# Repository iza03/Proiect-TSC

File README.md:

# DeskAssistant v1.5 – README

## Diagrama bloc

---

## Bill of Materials (BoM)

# Bill of Materials

| Componenta | Link |
|------------|------|
| SAMACSYS_PARTS_USB4110-GF-A | [https://componentsearchengine.com/part-view/USB4110-GF-A/GCT%20(GLOBAL%20CONNECTOR%20TECHNOLOGY)](https://componentsearchengine.com/part-view/USB4110-GF-A/GCT%20(GLOBAL%20CONNECTOR%20TECHNOLOGY)) |
| SI1308EDL-T1-GE3 | [https://componentsearchengine.com/part-view/SI1308EDL-T1-GE3/Vishay](https://componentsearchengine.com/part-view/SI1308EDL-T1-GE3/Vishay) |
| SJ | [https://grabcad.com/library/solder-jumpers-1](https://grabcad.com/library/solder-jumpers-1) |
| USBLC6-2SC6Y | [https://www.snapeda.com/parts/USBLC6-2SC6Y/STMicroelectronics/view-part/?ref=eda](https://www.snapeda.com/parts/USBLC6-2SC6Y/STMicroelectronics/view-part/?ref=eda) |
| W25Q512JVEIQ | [https://www.snapeda.com/parts/W25Q512JVEIQ/Winbond+Electronics/view-part/?ref=eda](https://www.snapeda.com/parts/W25Q512JVEIQ/Winbond+Electronics/view-part/?ref=eda) |
| ESP32_WROVER_EAGLE-LTSPICE_RR0402 | [https://www.snapeda.com/parts/RC0402FR-07226RL/Yageo/view-part/](https://www.snapeda.com/parts/RC0402FR-07226RL/Yageo/view-part/) |
| ESP32C6_VARISTORCN1812 | [https://www.mouser.co.uk/ProductDetail/EPCOS-TDK/B72520T0350K062?qs=dEfas%2FXlABIszF52uu7vrg%3D%3D](https://www.mouser.co.uk/ProductDetail/EPCOS-TDK/B72520T0350K062?qs=dEfas%2FXlABIszF52uu7vrg%3D%3D) |
| FH34SRJ-24S-0.5SH_99_ | [https://componentsearchengine.com/part-view/XC6220A331MR-G/Torex](https://componentsearchengine.com/part-view/XC6220A331MR-G/Torex) |
| MAX17048G+T10 | [https://www.snapeda.com/parts/MAX17048G+T10/Analog+Devices/view-part/?ref=eda](https://www.snapeda.com/parts/MAX17048G+T10/Analog+Devices/view-part/?ref=eda) |
| MBR0530 | [https://ro.mouser.com/ProductDetail/KYOCERA-AVX/SD0805S020S1R0?qs=jCA%252BPfw4LHbpkAoSnwrdjw%3D%3D](https://ro.mouser.com/ProductDetail/KYOCERA-AVX/SD0805S020S1R0?qs=jCA%252BPfw4LHbpkAoSnwrdjw%3D%3D) |
| PGB1010603MR | [https://www.snapeda.com/parts/PGB1010603MR/Littelfuse/view-part/?ref=eda](https://www.snapeda.com/parts/PGB1010603MR/Littelfuse/view-part/?ref=eda) |
| RCL_CPOL-EUCT3528 | [https://ro.mouser.com/ProductDetail/Vishay-Sprague/TR3B106K025C1300?qs=jCGqFXxTmLdffnuDkXzk1g%3D%3D](https://ro.mouser.com/ProductDetail/Vishay-Sprague/TR3B106K025C1300?qs=jCGqFXxTmLdffnuDkXzk1g%3D%3D) |
| 112A-TAAR-R03_ATTEND | [https://store.comet.bg/en/Catalogue/Product/43497/](https://store.comet.bg/en/Catalogue/Product/43497/) |
| 744043680IND_4828-WE-TPC_WRE | [https://www.digikey.sg/en/models/1638515](https://www.digikey.sg/en/models/1638515) |
| BD5229G-TR | [https://componentsearchengine.com/part-view/BD5229G-TR/ROHM%20Semiconductor](https://componentsearchengine.com/part-view/BD5229G-TR/ROHM%20Semiconductor) |
| DS3231SN | [https://www.snapeda.com/parts/DS3231SN%23/Analog+Devices/view-part/?ref=eda](https://www.snapeda.com/parts/DS3231SN%23/Analog+Devices/view-part/?ref=eda) |
| ESP32-C6-WROOM-1-N8 | [https://www.snapeda.com/parts/ESP32-C6-WROOM-1-N8/Espressif+Systems/view-part/?ref=eda](https://www.snapeda.com/parts/ESP32-C6-WROOM-1-N8/Espressif+Systems/view-part/?ref=eda) |
| MCP73831 | [https://www.digikey.com/en/models/1874108](https://www.digikey.com/en/models/1874108) |
| XC6220A331MR-G | [https://componentsearchengine.com/part-view/XC6220A331MR-G/Torex](https://componentsearchengine.com/part-view/XC6220A331MR-G/Torex) |
| QWIIC_CONNECTORJS-1MM | [https://www.snapeda.com/parts/PRT-14417/SparkFun/view-part/](https://www.snapeda.com/parts/PRT-14417/SparkFun/view-part/) |
| BUTTON_CUSYOMV1 | [https://industry.panasonic.com/global/en/downloads?tab=cad&small_g_cd=203&part_no=EVQPUJ02K&q=RVZRUFVKMDJLJTdDMTMlN0MyMDMlN0MzNDU5JTdDMSU3QyU3QyU3Q2ZhbHNl](https://industry.panasonic.com/global/en/downloads?tab=cad&small_g_cd=203&part_no=EVQPUJ02K&q=RVZRUFVKMDJLJTdDMTMlN0MyMDMlN0MzNDU5JTdDMSU3QyU3QyU3Q2ZhbHNl) |
| ESP32_WROVER_EAGLE-LTSPICE_CC0402 | [https://componentsearchengine.com/part-view/CC0402MRX5R5BB106/YAGEO](https://componentsearchengine.com/part-view/CC0402MRX5R5BB106/YAGEO) |
| CPH3225A | [https://www.snapeda.com/parts/CPH3225A/Seiko+Instruments/view-part/?ref=eda](https://www.snapeda.com/parts/CPH3225A/Seiko+Instruments/view-part/?ref=eda) |
| ADAFRUIT_LEDCHIP-LED0603 | [https://www.snapeda.com/parts/KP-1608SURCK/Kingbright/view-part/?ref=search&t=LED%200603](https://www.snapeda.com/parts/KP-1608SURCK/Kingbright/view-part/?ref=search&t=LED%200603) |
| ESP32_WROVER_BME680_BME680 | [https://www.snapeda.com/parts/BME680/Bosch/view-part/?welcome=home](https://www.snapeda.com/parts/BME680/Bosch/view-part/?welcome=home) |
| ESP32_WROVER_SPARKFUN-DISCRETESEMI_MOSFET_PCH-DMG2305UX-7 | [https://componentsearchengine.com/part-view/DMG2305UX-7/Diodes%20Incorporated](https://componentsearchengine.com/part-view/DMG2305UX-7/Diodes%20Incorporated) |

---

## Funcționalități hardware

### 1. Microcontroller – ESP32-C6-WROOM-1-N8
- **Wireless:** WiFi 6, BLE 5.0, Zigbee, Thread
- **Interfețe:** UART, I²C, SPI, USB, ADC, PWM
- **Rol:** Unitate centrală de control, achiziție date, comunicare cu periferice și backend.

### 2. Senzori
- **BME688**: măsoară temperatură, umiditate, presiune și compuși organici volatili (VOC)
  - **Interfață**: I²C
- **DS3231SN**: RTC (Real Time Clock)
  - **Interfață**: I²C
- **MAX17048**: fuel gauge pentru baterie
  - **Interfață**: I²C

### 3. Memorie externă
- **W25Q512JVEIQ**
  - **Tip**: NOR Flash, 512Mbit
  - **Interfață**: SPI

### 4. Managementul energiei
- **MCP73831**: încărcător Li-Ion
- **MAX17048**: monitorizare baterie
- **BD5229G-TR**: LDO pentru 2.9V stabil
- **Diodă Schottky, MOSFET, varistor**: protecție la supratensiuni și polarizare inversă

### 5. Conectivitate și I/O
- **USB4110-GF-A**: conector USB-C pentru alimentare/comunicare
- **QWIIC connector**: I²C modular pentru senzori plug-and-play
- **LED status** și **buton fizic** (boot/reset sau input utilizator)

---

## Conexiuni GPIO la ESP32-C6

| Componentă | Interfață | GPIO ESP32-C6 | Funcție |
|------------|-----------|----------------|---------|
| BME688 / DS3231 / MAX17048 | I²C | GPIO8 (SDA), GPIO9 (SCL) | Magistrală partajată |
| W25Q512JVEIQ | SPI | GPIO4 (MOSI), GPIO5 (MISO), GPIO6 (CLK), GPIO7 (CS) | Comunicare cu flash extern |
| LED status | GPIO | GPIO3 | Indicator status / PWM |
| Buton | GPIO + Pull-up | GPIO0 | Reset / boot / input utilizator |
| MCP73831 – STAT | GPIO | GPIO10 | Monitorizare stare încărcare |
| MAX17048 – ALERT | GPIO (Interrupt) | GPIO1 | Notificare SoC critic |
| USB-C – D+ / D- | USB | GPIO18 (D+), GPIO19 (D-) | Comunicare USB nativă |

---

## Estimare consum energetic

| Componentă | Consum tipic |
|------------|--------------|
| ESP32-C6 | ~130 mA (activ) |
| BME688 | ~3.1 µA |
| DS3231 | ~200 nA |
| MAX17048 | ~23 µA |
| MCP73831 | până la 500 mA (în încărcare) |
| LED-uri | 2–10 mA |

**Consum total în mod activ:** aprox. **150–180 mA**

### Randări PCB și design fizic

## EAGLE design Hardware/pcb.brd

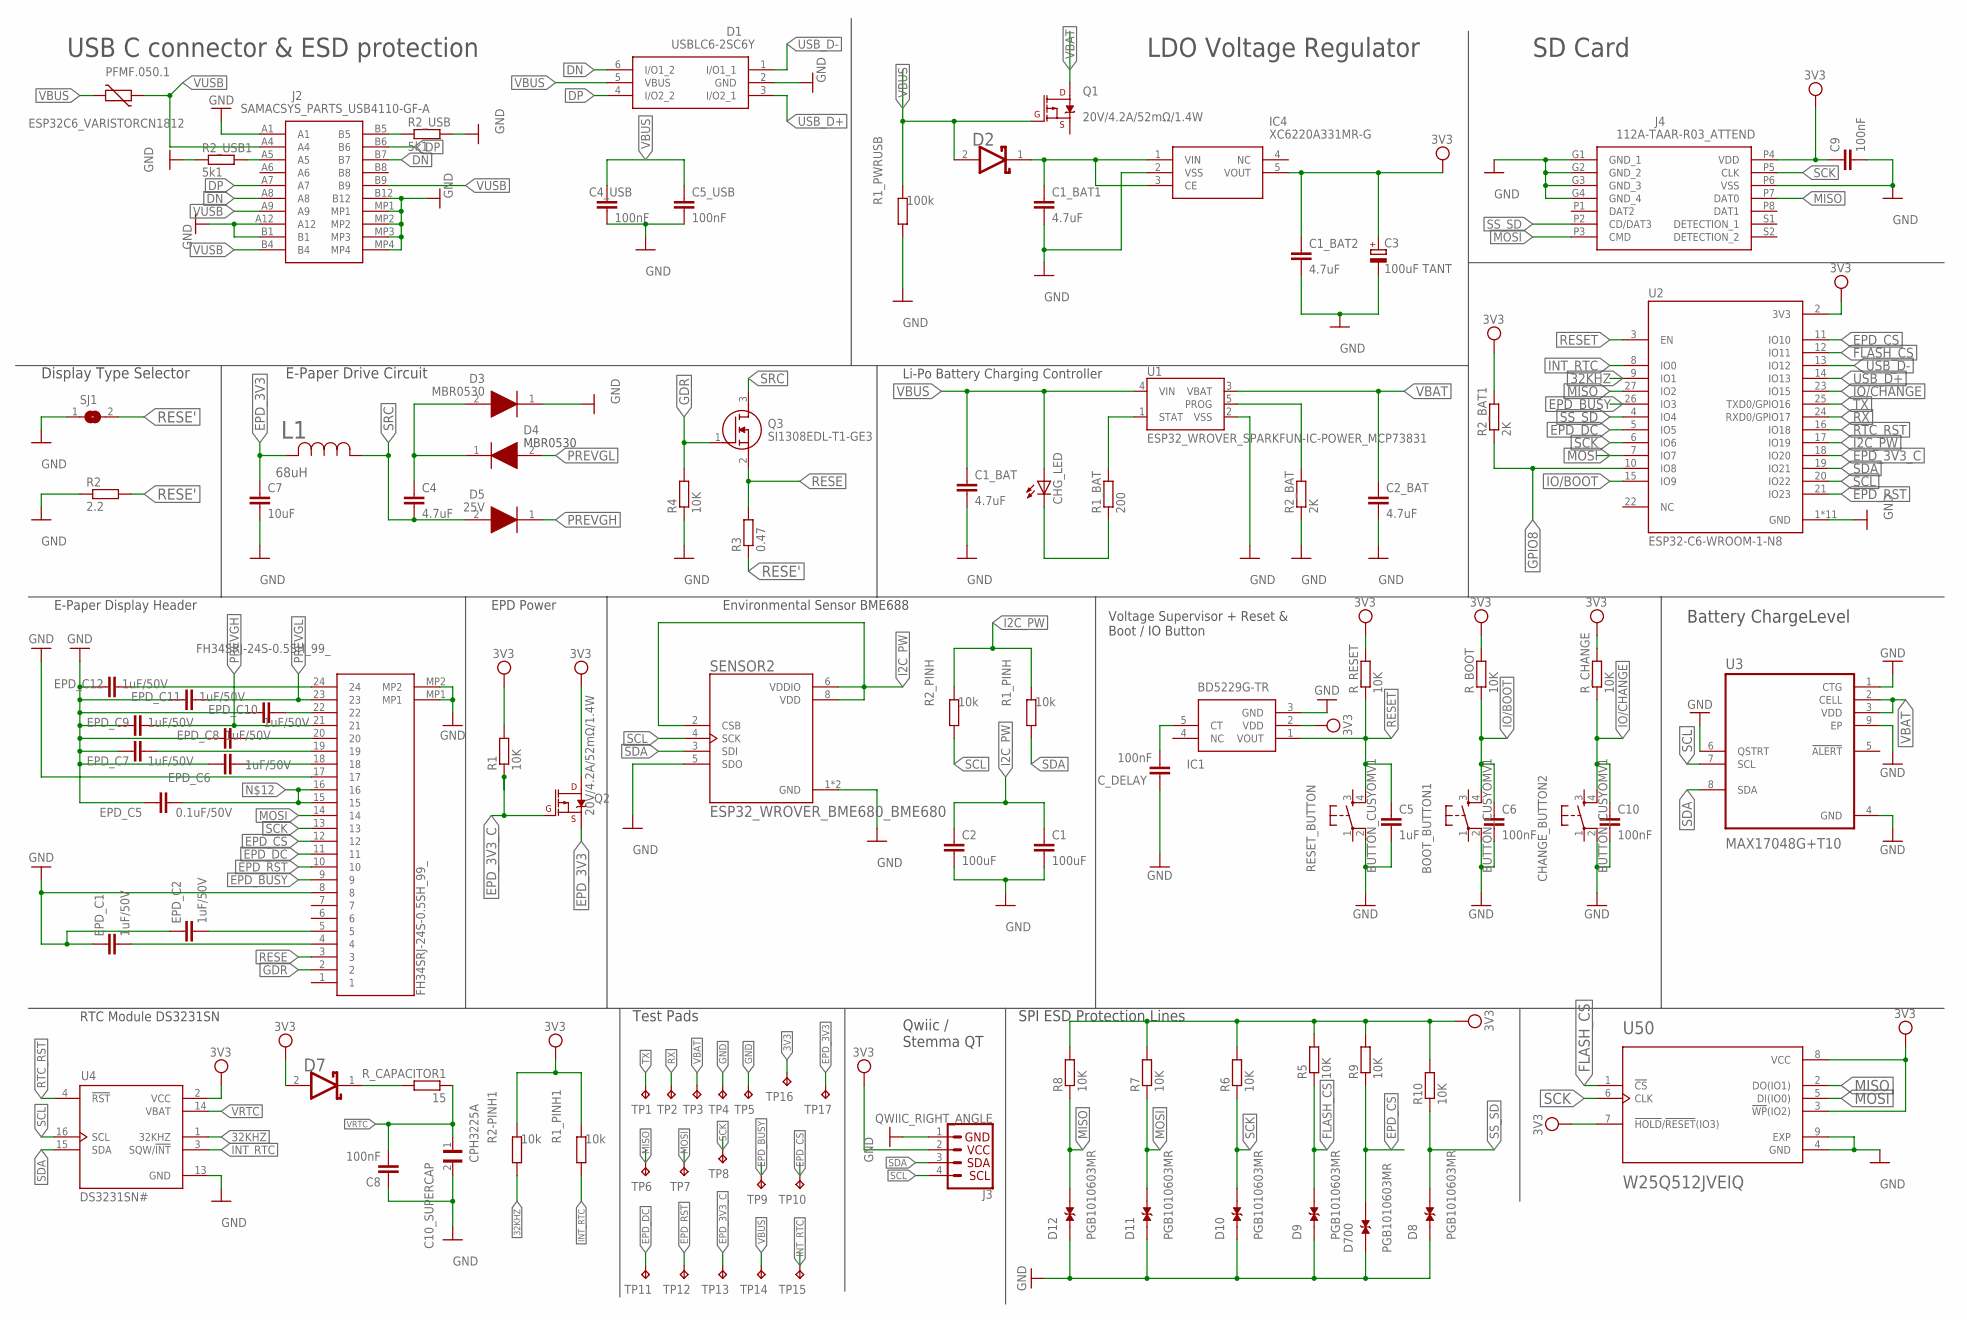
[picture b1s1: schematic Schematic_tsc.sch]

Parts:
BOOT_BUTTON1: BUTTON_CUSYOMV1; MYBUTTON
C1, C2: 100uF; EAGLE-LTSPICE_C0402
C1_BAT, C1_BAT1, C1_BAT2, C2_BAT, C4: 4.7uF; EAGLE-LTSPICE_C0402
C3: 100uF TANT; RCL_CT3528
C4_USB, C5_USB, C6, C8, C9, C10: 100nF; EAGLE-LTSPICE_C0402
C5: 1uF; EAGLE-LTSPICE_C0402
C7: 10uF; EAGLE-LTSPICE_C0402
C10_SUPERCAP: CPH3225A; CAPCP3225X100N
CHANGE_BUTTON2: BUTTON_CUSYOMV1; MYBUTTON
CHG_LED: ADAFRUIT_LEDCHIP-LED0603; ADAFRUIT_CHIP-LED0603
C_DELAY: 100nF; EAGLE-LTSPICE_C0402
D1: USBLC6-2SC6Y; SOT95P280X145-6N
D2, D7: ESP32_WROVER_AVX---SD0805S020S1R0_AVX_SD0805S020S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; ESP32_WROVER_AVX---SD0805S020S1R0_AVX_SD0805S020S1R0_0
D3, D4: MBR0530; SOD3716X135N
D5: 25V; SOD3716X135N
D8, D9, D10, D11, D12, D700: PGB1010603MR; DIOC1608X36N
EPD_C1, EPD_C2, EPD_C6, EPD_C7, EPD_C8, EPD_C9, EPD_C10, EPD_C11, EPD_C12: 1uF/50V; EAGLE-LTSPICE_C0402
EPD_C5: 0.1uF/50V; EAGLE-LTSPICE_C0402
FH34SRJ-24S-0.5SH_99_: FH34SRJ-24S-0.5SH_99_; FH34SRJ24S05SH99
IC1: BD5229G-TR; SOT95P280X125-5N
IC4: XC6220A331MR-G; SOT95P280X120-5N
J2: SAMACSYS_PARTS_USB4110-GF-A; SAMACSYS_PARTS_USB4110GFA
J3: QWIIC_RIGHT_ANGLE; JST04_1MM_RA
J4: 112A-TAAR-R03_ATTEND; 112ATAARR03ATTEND
L1: 68uH; IND_4828-WE-TPC_WRE
PFMF.050.1: ESP32C6_VARISTORCN1812; ESP32C6_VARISTOR_CT/CN1812
Q1, Q2: 20V/4.2A/52mΩ/1.4W; ESP32_WROVER_SPARKFUN-DISCRETESEMI_SOT23-3
Q3: SI1308EDL-T1-GE3; SOT65P210X110-3N
R1, R4, R5, R6, R7, R8, R9, R10: 10K; ESP32_WROVER_EAGLE-LTSPICE_R0402
R1_BAT: 200; ESP32_WROVER_EAGLE-LTSPICE_R0402
R1_PINH, R1_PINH1, R2-PINH1, R2_PINH: 10k; ESP32_WROVER_EAGLE-LTSPICE_R0402
R1_PWRUSB: 100k; ESP32_WROVER_EAGLE-LTSPICE_R0402
R2: 2.2; ESP32_WROVER_EAGLE-LTSPICE_R0402
R2_BAT, R2_BAT1: 2K; ESP32_WROVER_EAGLE-LTSPICE_R0402
R2_USB, R2_USB1: 5k1; ESP32_WROVER_EAGLE-LTSPICE_R0402
R3: 0.47; ESP32_WROVER_EAGLE-LTSPICE_R0402
RESET_BUTTON: BUTTON_CUSYOMV1; MYBUTTON
R_BOOT: 10K; ESP32_WROVER_EAGLE-LTSPICE_R0402
R_CAPACITOR1: 15; ESP32_WROVER_EAGLE-LTSPICE_R0402
R_CHANGE: 10K; ESP32_WROVER_EAGLE-LTSPICE_R0402
R_RESET: 10K; ESP32_WROVER_EAGLE-LTSPICE_R0402
SENSOR2: ESP32_WROVER_BME680_BME680; ESP32_WROVER_BME680_PSON80P300X300X100-8N
SJ1: SJ
TP1, TP2, TP3, TP4, TP5, TP6, TP7, TP8, TP9, TP10, TP11, TP12, TP13, TP14, TP15, TP16, TP17: TPTP20R; TP20R
U1: ESP32_WROVER_SPARKFUN-IC-POWER_MCP73831; ESP32_WROVER_SPARKFUN-IC-POWER_SOT23-5
U2: ESP32-C6-WROOM-1-N8; XCVR_ESP32-C6-WROOM-1-N8
U3: MAX17048G+T10; SON50P200X200X80-9N
U4: DS3231SN#; SOIC127P1032X265-16N
U50: W25Q512JVEIQ; SON127P600X800X80-9N

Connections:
3V3: C1_BAT2.1, C3.+, C9.1, D7.2 (ANODE), IC1.2 (VDD), IC4.5 (VOUT), J3.2, J4.P4 (VDD), Q2.3 (D), R1.2, R1_PINH1.2, R2-PINH1.2, R2_BAT1.2, R5.2, R6.2, R7.2, R8.2, R9.2, R10.2, R_BOOT.2, R_CHANGE.2, R_RESET.2, TP16.TP, U2.2 (3V3), U4.2 (VCC), U50.3 (!WP!(IO2)), U50.7 (!HOLD!/!RESET!(IO3)), U50.8 (VCC)
32KHZ: R2-PINH1.1, U2.9 (IO1), U4.1 (32KHZ)
DN: D1.6 (I/O1_2), J2.A8, J2.B7
DP: D1.4 (I/O2_2), J2.A7, J2.B6
EPD_3V3: C7.1, L1.2, Q2.2 (S), TP17.TP
EPD_3V3_C: Q2.1 (G), R1.1, TP13.TP, U2.18 (IO20)
EPD_BUSY: FH34SRJ-24S-0.5SH_99_.9, TP9.TP, U2.26 (IO3)
EPD_CS: D700.2, FH34SRJ-24S-0.5SH_99_.12, R9.1, TP10.TP, U2.11 (IO10)
EPD_DC: FH34SRJ-24S-0.5SH_99_.11, TP11.TP, U2.5 (IO5)
EPD_RST: FH34SRJ-24S-0.5SH_99_.10, TP12.TP, U2.21 (IO23)
FLASH_CS: D9.2, R5.1, U2.12 (IO11), U50.1 (!CS)
GDR: FH34SRJ-24S-0.5SH_99_.2, Q3.1 (G), R4.2
GND: BOOT_BUTTON1.2, C1.2, C1_BAT.2, C1_BAT1.2, C1_BAT2.2, C2.2, C2_BAT.2, C3.-, C4_USB.2, C5.2, C5_USB.2, C6.2, C7.2, C8.1, C9.2, C10.2, C10_SUPERCAP.2, CHANGE_BUTTON2.2, C_DELAY.1, D1.2 (GND), D3.1 (K), D8.1, D9.1, D10.1, D11.1, D12.1, D700.1, EPD_C1.1, EPD_C2.1, EPD_C5.1, EPD_C6.1, EPD_C7.1, EPD_C8.1, EPD_C9.1, EPD_C10.1, EPD_C11.1, EPD_C12.1, FH34SRJ-24S-0.5SH_99_.8, FH34SRJ-24S-0.5SH_99_.17, FH34SRJ-24S-0.5SH_99_.MP1, FH34SRJ-24S-0.5SH_99_.MP2, IC1.3 (GND), IC4.2 (VSS), J2.A1, J2.A12, J2.B1, J2.B12, J2.MP1, J2.MP2, J2.MP3, J2.MP4, J3.1, J4.G1 (GND_1), J4.G2 (GND_2), J4.G3 (GND_3), J4.G4 (GND_4), J4.P6 (VSS), R1_PWRUSB.1, R2.1, R2_BAT.1, R2_USB.2, R2_USB1.1, R4.1, RESET_BUTTON.2, SENSOR2.1 (GND), SENSOR2.5 (SDO), SENSOR2.7 (GND), SJ1.1, TP4.TP, TP5.TP, U1.2 (VSS), U2.1 (GND), U2.28 (GND), U2.29_1 (GND), U2.29_2 (GND), U2.29_3 (GND), U2.29_4 (GND), U2.29_5 (GND), U2.29_6 (GND), U2.29_7 (GND), U2.29_8 (GND), U2.29_9 (GND), U3.1 (CTG), U3.4 (GND), U3.6 (QSTRT), U3.9 (EP), U4.13 (GND), U50.4 (GND), U50.9 (EXP)
GPIO8: R2_BAT1.1, U2.10 (IO8)
I2C_PW: C1.1, C2.1, R1_PINH.2, R2_PINH.2, SENSOR2.2 (CSB), SENSOR2.6 (VDDIO), SENSOR2.8 (VDD), U2.17 (IO19)
INT_RTC: R1_PINH1.1, TP15.TP, U2.8 (IO0), U4.3 (SQW/!INT)
IO/BOOT: BOOT_BUTTON1.4, C6.1, R_BOOT.1, U2.15 (IO9)
IO/CHANGE: C10.1, CHANGE_BUTTON2.4, R_CHANGE.1, U2.23 (IO15)
MISO: D12.2, J4.P7 (DAT0), R8.1, TP6.TP, U2.27 (IO2), U50.2 (DO(IO1))
MOSI: D11.2, FH34SRJ-24S-0.5SH_99_.14, J4.P3 (CMD), R7.1, TP7.TP, U2.7 (IO7), U50.5 (DI(IO0))
unnamed: J2.A5, R2_USB1.2
unnamed: J2.B5, R2_USB.1
unnamed: C1_BAT1.1, D2.1 (CATHODE), IC4.1 (VIN), IC4.3 (CE)
unnamed: EPD_C12.2, FH34SRJ-24S-0.5SH_99_.24
unnamed: C4.1, D3.2 (A), D4.1 (K)
unnamed: R1_BAT.2, U1.1 (STAT)
unnamed: CHG_LED.C, R1_BAT.1
unnamed: R2_BAT.2, U1.5 (PROG)
unnamed: EPD_C10.2, FH34SRJ-24S-0.5SH_99_.22
unnamed: EPD_C5.2, FH34SRJ-24S-0.5SH_99_.15, FH34SRJ-24S-0.5SH_99_.16
unnamed: EPD_C7.2, FH34SRJ-24S-0.5SH_99_.19
unnamed: EPD_C6.2, FH34SRJ-24S-0.5SH_99_.18
unnamed: EPD_C2.2, FH34SRJ-24S-0.5SH_99_.5
unnamed: EPD_C1.2, FH34SRJ-24S-0.5SH_99_.4
unnamed: C_DELAY.2, IC1.5 (CT)
unnamed: D7.1 (CATHODE), R_CAPACITOR1.2
unnamed: EPD_C8.2, FH34SRJ-24S-0.5SH_99_.20
PREVGH: D5.1 (K), EPD_C9.2, FH34SRJ-24S-0.5SH_99_.21
PREVGL: D4.2 (A), EPD_C11.2, FH34SRJ-24S-0.5SH_99_.23
RESE: FH34SRJ-24S-0.5SH_99_.3, Q3.2 (S), R3.2
RESE': R2.2, R3.1, SJ1.2
RESET: C5.1, IC1.1 (VOUT), RESET_BUTTON.4, R_RESET.1, U2.3 (EN)
RTC_RST: U2.16 (IO18), U4.4 (!RST)
RX: TP2.TP, U2.24 (RXD0/GPIO17)
SCK: D10.2, FH34SRJ-24S-0.5SH_99_.13, J4.P5 (CLK), R6.1, TP8.TP, U2.6 (IO6), U50.6 (CLK)
SCL: J3.4, R2_PINH.1, SENSOR2.4 (SCK), U2.20 (IO22), U3.7 (SCL), U4.16 (SCL)
SDA: J3.3, R1_PINH.1, SENSOR2.3 (SDI), U2.19 (IO21), U3.8 (SDA), U4.15 (SDA)
SRC: C4.2, D5.2 (A), L1.1, Q3.3 (D)
SS_SD: D8.2, J4.P2 (CD/DAT3), R10.1, U2.4 (IO4)
TX: TP1.TP, U2.25 (TXD0/GPIO16)
USB_D+: D1.3 (I/O2_1), U2.14 (IO13)
USB_D-: D1.1 (I/O1_1), U2.13 (IO12)
VBAT: C2_BAT.1, Q1.3 (D), TP3.TP, U1.3 (VBAT), U3.2 (CELL), U3.3 (VDD)
VBUS: C1_BAT.1, C4_USB.1, C5_USB.1, CHG_LED.A, D1.5 (VBUS), D2.2 (ANODE), PFMF.050.1.2, Q1.1 (G), R1_PWRUSB.2, TP14.TP, U1.4 (VIN)
VRTC: C8.2, C10_SUPERCAP.1, R_CAPACITOR1.1, U4.14 (VBAT)
VUSB: J2.A4, J2.A9, J2.B4, J2.B9, PFMF.050.1.1

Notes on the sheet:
SD Card
LDO Voltage Regulator
USB C connector & ESD protection
Display Type Selector
E-Paper Drive Circuit
Li-Po Battery Charging Controller
E-Paper Display Header
EPD Power
Environmental Sensor BME688
Voltage Supervisor + Reset & Boot / IO Button
RTC Module DS3231SN
Test Pads
Qwiic / Stemma QT
SPI ESD Protection Lines
Battery ChargeLevel

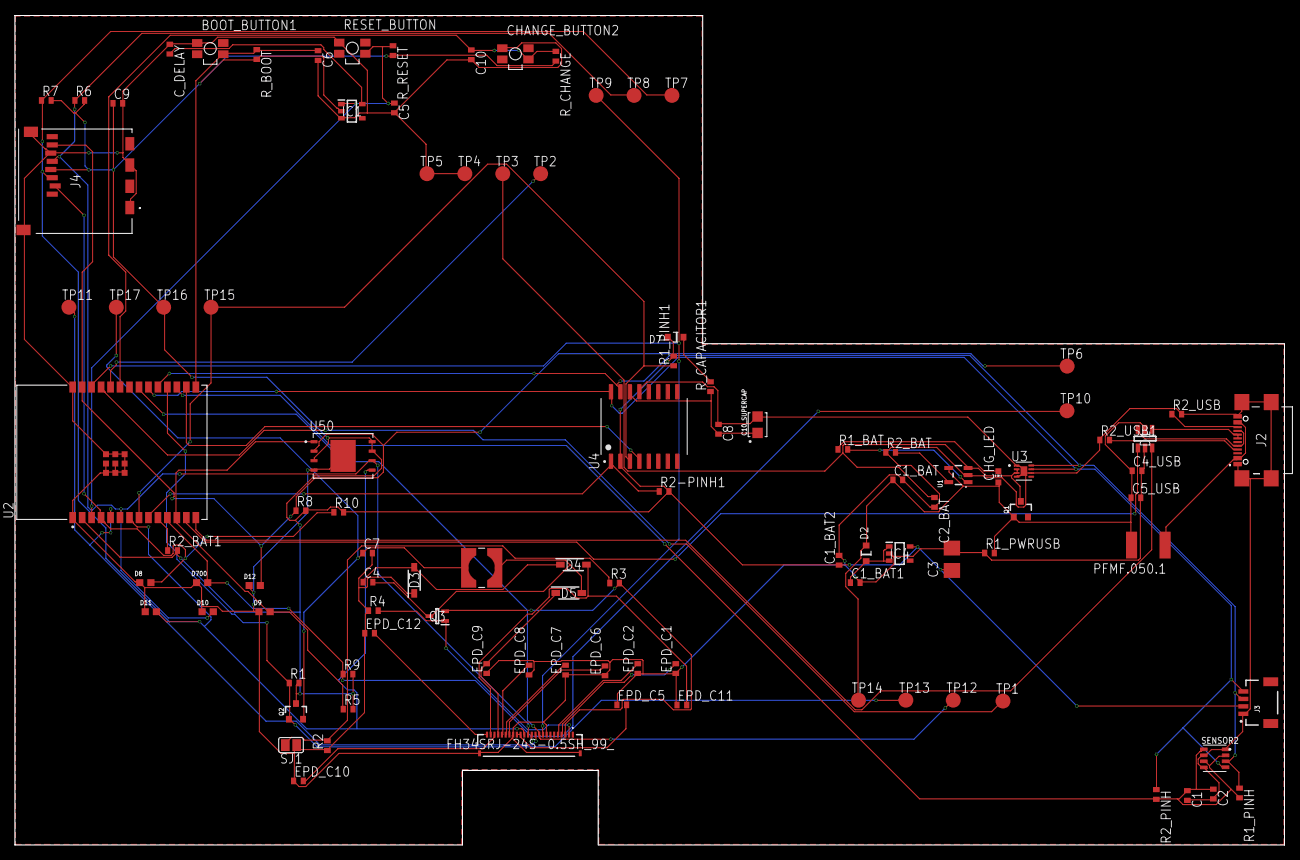
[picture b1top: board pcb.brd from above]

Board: 2 copper layers, 170.2 x 111.2 mm, 103 parts (0 on the bottom side), 56 nets.

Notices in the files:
parts and their libraries:
DeskAssistant v19 v1: COPYRIGHT: Copyright (C) 2024 Ultra Librarian. All rights reserved.
